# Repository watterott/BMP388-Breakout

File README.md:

# BMP388-Breakout
Breakout with BMP388 Digital Absolute Barometric Pressure Sensor from Bosch Sensortec.

* [Bosch BMP388](https://www.bosch-sensortec.com/bst/products/all_products/BMP388) Absolute Barometric Pressure Sensor
* Pressure Range: 300...1100hPa (+9000...-500m above/below sea level)
* On-board 3.3V voltage regulator
* SPI Interface (up to 10MHz)
* TWI/I2C Interface (address 0x76 when SDO=0 or 0x77 when SDO=1, CS=1 for I2C)
* 3.3V - 5V Power Supply and Logic Level
* Open-Source and released under the [Creative Commons Attribution Share-Alike License](https://creativecommons.org/licenses/by-sa/4.0/).
* **[Documentation on learn.watterott.com](https://learn.watterott.com)**

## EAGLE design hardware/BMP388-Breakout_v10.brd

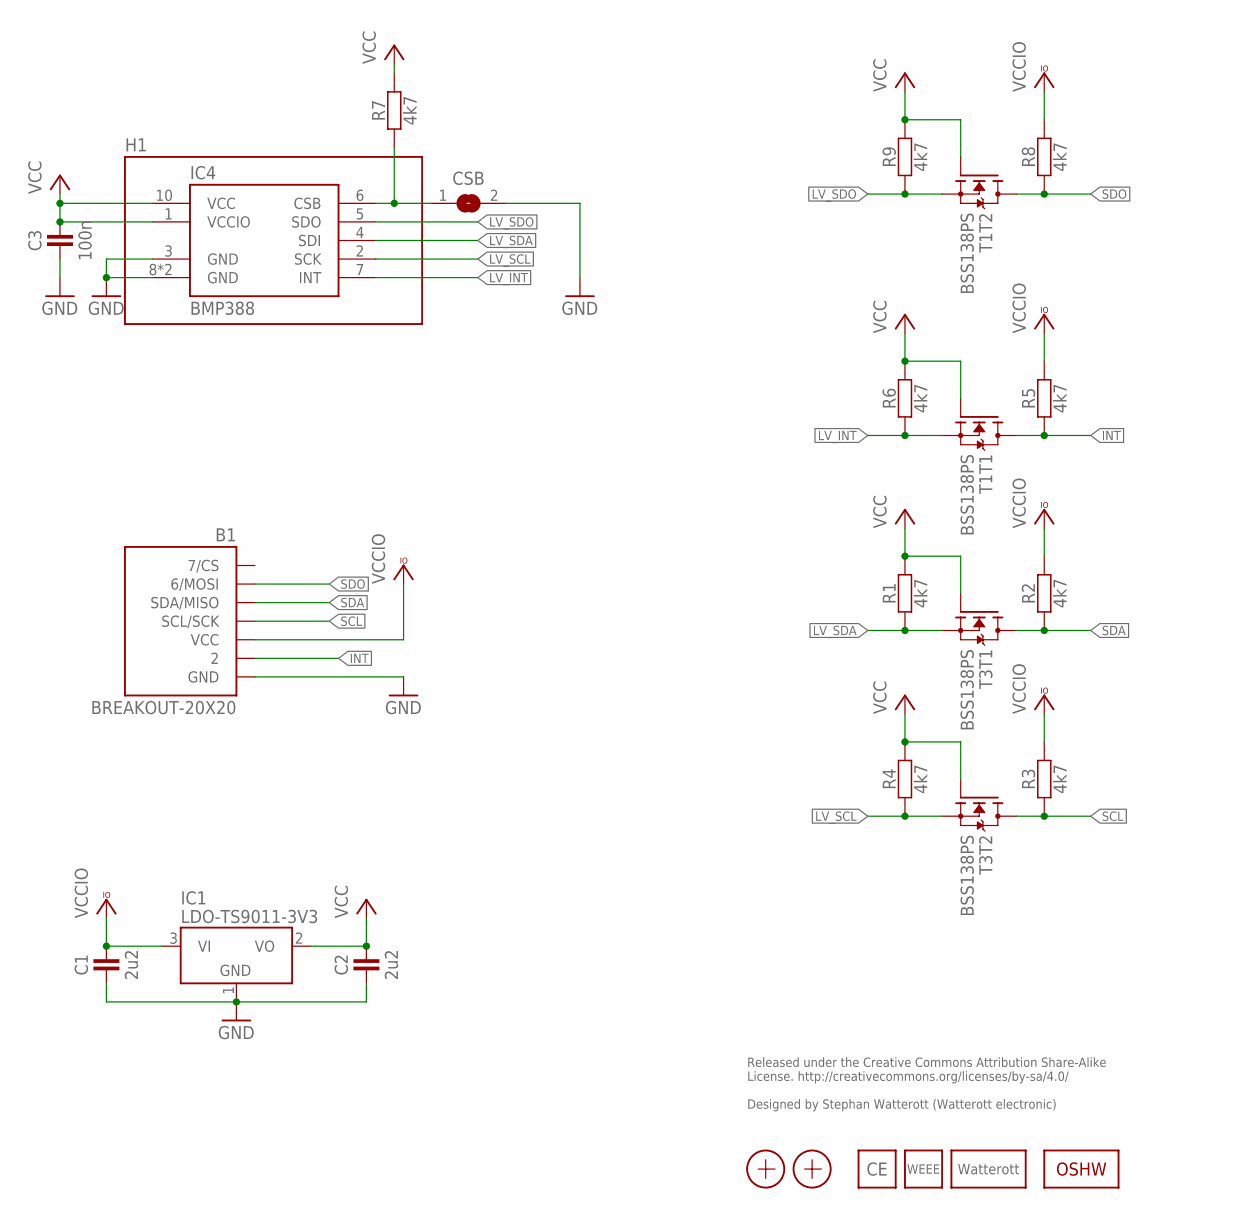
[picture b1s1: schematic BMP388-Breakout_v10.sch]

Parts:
B1: BREAKOUT-20X20
C1, C2: 2u2; C0402
C3: 100n; C0402
CSB: JUMPER2-0603-NC; JUMPER2-0603_NC
H1: SF2
IC1: LDO-TS9011-3V3; SOT23
IC4: BMP388
LOGO2: OSHW_LOGOX0070; OSHW_6X70
LOGO3: LOGO_WEEE-4; WEEE_4MM
LOGO4: LOGO_CE-4; CE_4MM
LOGO5: LOGO_SPARK-4; SPARK_4MM
R1, R2, R3, R4, R5, R6, R7, R8, R9: 4k7; C0402
T1, T3: BSS138PS; SOT363
X1, X2: PASSER-07; PASSER_07MM

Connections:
GND: B1.GND, C1.1, C2.1, C3.1, CSB.2, IC1.1 (GND), IC4.3 (GND), IC4.8 (GND), IC4.9 (GND)
INT: B1.2, R5.1, T1.6 (D)
LV_INT: IC4.7 (INT), R6.1, T1.1 (S)
LV_SCL: IC4.2 (SCK), R4.1, T3.4 (S)
LV_SDA: IC4.4 (SDI), R1.1, T3.1 (S)
LV_SDO: IC4.5 (SDO), R9.1, T1.4 (S)
unnamed: CSB.1, IC4.6 (CSB), R7.1
SCL: B1.SCL/SCK, R3.1, T3.3 (D)
SDA: B1.SDA/MISO, R2.1, T3.6 (D)
SDO: B1.MOSI (6/MOSI), R8.1, T1.3 (D)
VCC: C2.2, C3.2, IC1.2 (VO), IC4.1 (VCCIO), IC4.10 (VCC), R1.2, R4.2, R6.2, R7.2, R9.2, T1.2 (G), T1.5 (G), T3.2 (G), T3.5 (G)
VCCIO: B1.VCC, C1.2, IC1.3 (VI), R2.2, R3.2, R5.2, R8.2

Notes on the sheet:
Released under the Creative Commons Attribution Share-Alike License. http://creativecommons.org/licenses/by-sa/4.0/ Designed by Stephan Watterott (Watterott electronic)

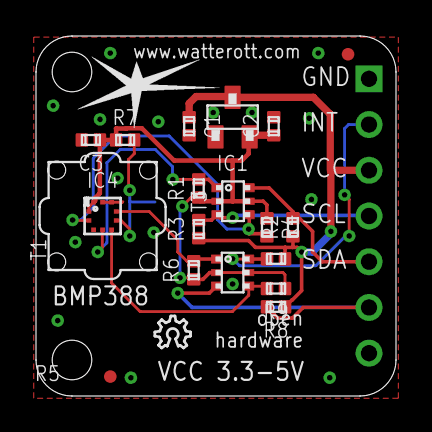
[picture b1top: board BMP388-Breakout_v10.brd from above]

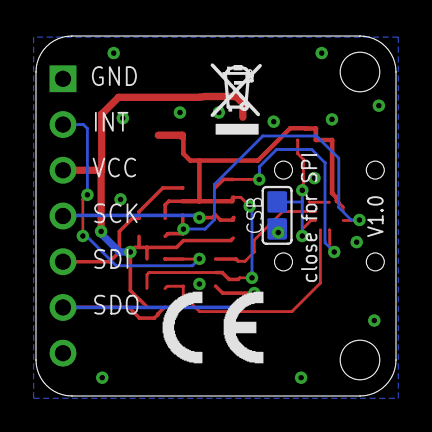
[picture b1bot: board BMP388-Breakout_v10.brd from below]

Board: 2 copper layers, 20.0 x 20.0 mm, 25 parts (3 on the bottom side), 12 nets.

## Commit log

2019-02-02 added readme
2019-10-01 added layout and schematics
